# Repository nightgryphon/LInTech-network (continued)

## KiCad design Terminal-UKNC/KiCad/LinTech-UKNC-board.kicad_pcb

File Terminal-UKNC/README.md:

# LInTech - плата Терминальной Машины (ТМ) - клиента УКНЦ (Электроника МС 0511)

Плата воссоздана [Night Gryphon](https://github.com/nightgryphon) по имеющемуся у него в наличии оригиналу платы.

Прошивка платы маркирована "КЛС-ТМ-BD1 П1 В1 Т03"

Содержание:
- KiCad - исходный проект реконструкции платы в формате KiCad
- Gerbers - GERBER файлы для изготовления реплики
- LinTech-UKNC-board-BOM.html - BOM, список компонентов
- LinTech-UKNC-board.pdf - реконструированая схема платы
- Firmware - микропрограмма контроллера Intel 8031
- Reference_Photo - фото платы

На данный момент реальные платы по данной реконструкции не изготавливались / не тестировались, в проекте возможны неточности.

## Техническое описание
**[WIP]**

Плата устанавливается в боковой разъем СА вместо штатной сетевой карты УКНЦ и подключается к сети обычным (существующим) кабелем через стандартную коммутационную коробку учебной сети УКНЦ.

Плата построена на базе микроконтроллера Intel 8031 (ДД1).
 
Программа контроллера размещена во внешнем ПЗУ (ДД6). ОЗУ контроллера расширено 573РУ10 (ДД5). 

Адресное пространство памяти данных контроллера разделено на 2 части:
- В младшей части расположено дополнительное ОЗУ
- В старшей - порты контроллера 580ВВ55А (ДД13)

Обмен с линией осуществляется по последовательному порту (RXD/TXD)

На порт Р1 выведены сигналы шины периферийного процессора УКНЦ:
0. SYNC
1. DIN 
2. DOUT
3. WTBT
4. RPLY
5. DMGO
6. DMR 
7. SACK

**[ToDo]**
Описание работы с МПИ/QBUS и прерываний

MCU Р3.5 - разрешение векторных прерываний
ДД12 - адрес векторного прерывания ( 0b 1110 0x00 ; x = ~ ВВ55-PC.7)

### Интерфейс УКНЦ
[ToDo]

## Описание микропрограммы
[Требуется помощь]

## Сетевой протокол
[Требуется помощь]

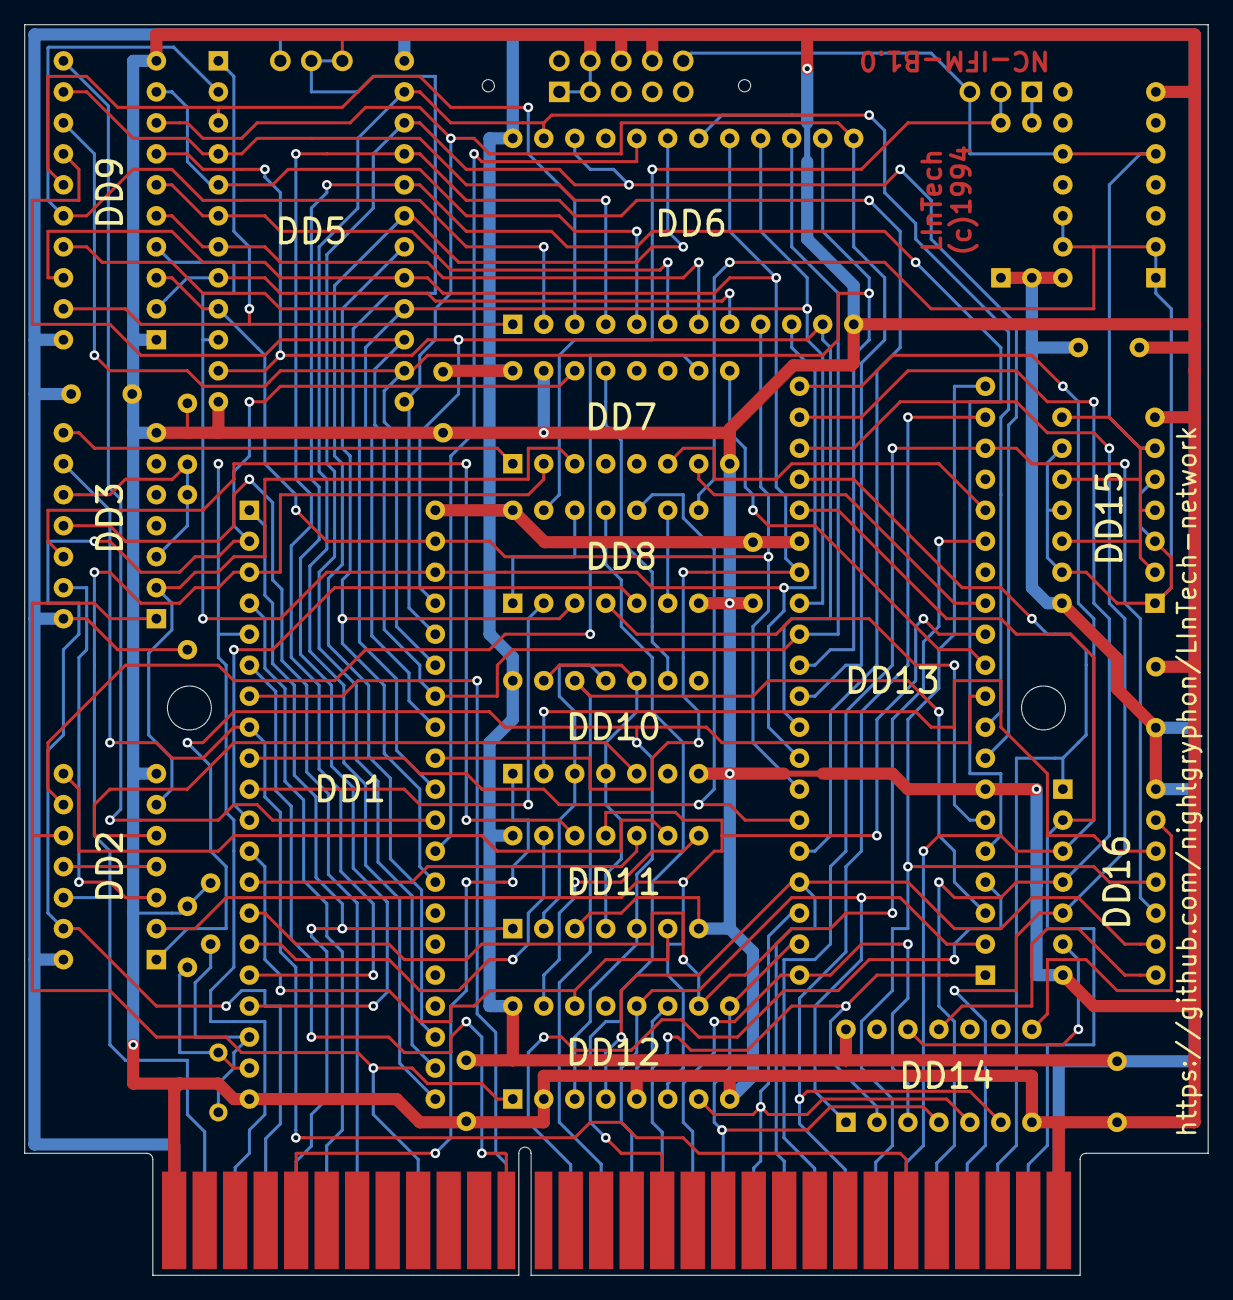
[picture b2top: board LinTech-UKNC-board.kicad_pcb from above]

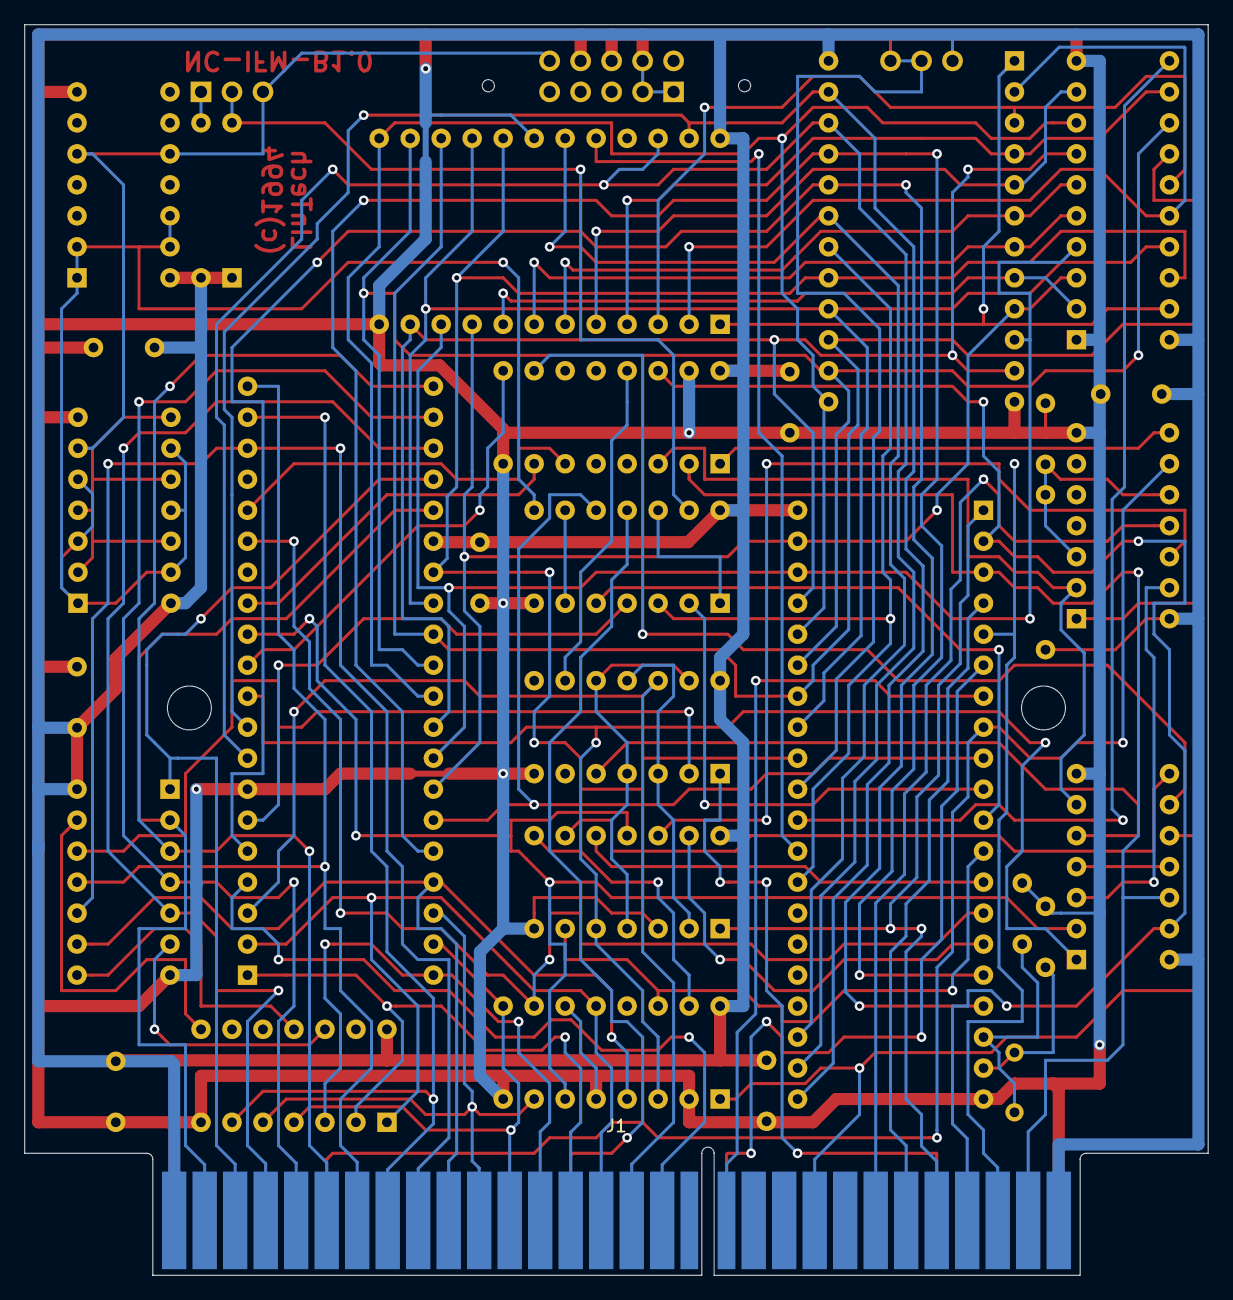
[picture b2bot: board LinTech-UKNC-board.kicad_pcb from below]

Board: 2 copper layers, 97.0 x 102.5 mm, 34 parts (2 on the bottom side), 93 nets.

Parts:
C1, C2: 18pf; C_Disc_D5.0mm_W2.5mm_P5.00mm
C3: 160pf; C_Disc_D5.0mm_W2.5mm_P5.00mm
C4, C5, C6, C7, C8, C9, C10: 150nf; C_Disc_D5.0mm_W2.5mm_P5.00mm
D1: КД522Б; D_A-405_P12.70mm_Horizontal
DD1: i8031; DIP-40_W15.24mm
DD2: 1533LA3; DIP-14_W7.62mm
DD3: 1533LA9; DIP-14_W7.62mm
DD5: 537RU10; DIP-24_W15.24mm
DD6: 573RF5; DIP-24_W15.24mm
DD7: 555ID4; DIP-16_W7.62mm
DD8: 1533LN1; DIP-14_W7.62mm
DD9: 1533IR22; DIP-20_W7.62mm
DD10: 555TM2; DIP-14_W7.62mm
DD11: 555LN1; DIP-14_W7.62mm
DD12: 1533KP11; DIP-16_W7.62mm
DD13: 580VV55A; DIP-40_W15.24mm
DD14: 1533LA2; DIP-14_W7.62mm
DD15: 155LP9; DIP-14_W7.62mm
DD16: 1533LE4; DIP-14_W7.62mm
J1: UKNC-CA
JP1: Jumper_3_Bridged12
LAN1: ОНП-КГ-56-10/33х7,4-В53; PinHeader_2x05_P2.54mm_Horizontal
Q1: КТ315Г; PinHeader_1x03_P2.54mm_Vertical
R1: 15K; R_Axial_DIN0309_L9.0mm_D3.2mm_P12.70mm_Horizontal
R2: 4K3; R_Axial_DIN0309_L9.0mm_D3.2mm_P12.70mm_Horizontal
WS1: DIP-14_W7.62mm
Y1: 12MHz; Crystal_HC18-U_Horizontal

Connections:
+5V: C4.2, C5.2, C6.2, C7.2, C8.1, C9.2, C10.2, D1.1, DD1.40, DD2.14, DD3.14, DD5.24, DD6.24, DD7.16, DD8.14, DD9.20, DD10.14, DD11.14, DD12.16, DD13.26, DD14.14, DD15.14, DD16.14, J1.1, J1.59, JP1.3, R1.1, R2.1, WS1.14
A16: DD10.1, J1.10
AD0: DD13.4, J1.27
AD1: DD10.12, DD13.3, J1.29
AD2: DD12.12, DD13.2, DD14.1, J1.31
AD3: DD13.1, DD14.2, J1.33
AD4: DD13.40, DD14.3, J1.35
AD5: DD12.9, DD13.39, DD14.4, J1.37
AD6: DD12.7, DD13.38, DD14.5, J1.39
AD7: DD12.4, DD13.37, DD16.9, J1.41
AD8: DD13.18, DD16.10, J1.43
AD9: DD13.19, DD14.6, J1.45
AD10: DD13.20, DD16.11, J1.47
AD11: DD13.21, DD16.3, J1.49
AD12: DD13.22, DD16.4, J1.51
AD13: DD13.23, DD16.5, J1.53
AD14: DD13.24, DD16.1, J1.55
AD15: DD13.25, DD16.2, J1.57
ALCO: DD8.11, J1.34
DIN: DD1.2, DD2.13, DD7.14, J1.7
DMGO: DD1.7, J1.23
DMR: DD1.6, J1.24
DOUT: DD1.3, DD2.12, DD7.2, J1.3
GND: C1.2, C2.2, C3.1, C4.1, C5.1, C6.1, C7.1, C8.2, C9.1, C10.1, DD1.20, DD2.7, DD3.7, DD5.12, DD6.12, DD6.18, DD7.8, DD7.15, DD8.7, DD9.1, DD9.10, DD10.7, DD11.3, DD11.7, DD12.2, DD12.5, DD12.8, DD12.11, DD13.7, DD14.7, DD15.7, DD16.7, J1.2, J1.60, JP1.1, LAN1.1, LAN1.3, LAN1.4, LAN1.6, LAN1.8, WS1.7
IAKO: DD2.10, DD3.1, DD12.1, J1.17
MCU_A8: DD1.21, DD5.23, DD6.23, DD13.9
MCU_A9: DD1.22, DD5.22, DD6.22, DD13.8
MCU_A10: DD1.23, DD5.19, DD6.19
MCU_A15: DD1.28, DD5.18, DD8.3
MCU_AD0: DD1.39, DD5.9, DD6.9, DD9.3, DD13.34
MCU_AD1: DD1.38, DD5.10, DD6.10, DD9.4, DD13.33
MCU_AD2: DD1.37, DD5.11, DD6.11, DD9.7, DD13.32
MCU_AD3: DD1.36, DD5.13, DD6.13, DD9.8, DD13.31
MCU_AD4: DD1.35, DD5.14, DD6.14, DD9.13, DD13.30
MCU_AD5: DD1.34, DD5.15, DD6.15, DD9.14, DD13.29
MCU_AD6: DD1.33, DD5.16, DD6.16, DD9.17, DD13.28
MCU_AD7: DD1.32, DD5.17, DD6.17, DD9.18, DD13.27
MCU_ALE: DD1.30, DD9.11
MCU_EA: DD1.31, JP1.2
MCU_INT0: DD1.12, DD11.6, DD12.14
MCU_INT1: DD1.13, DD11.10
MCU_P3-4: DD1.14, DD12.10, DD13.15
MCU_P3-5: DD1.15, DD11.13
MCU_PSEN: DD1.29, DD6.20
MCU_RD: DD1.17, DD5.20, DD13.5
MCU_RESET: DD1.9, DD8.10, DD13.35
MCU_RXD: DD1.10, DD8.2
MCU_TXD: DD1.11, DD8.5
MCU_WR: DD1.16, DD5.21, DD13.36
M_A0: DD5.8, DD6.8, DD9.2
M_A1: DD5.7, DD6.7, DD9.5
M_A2: DD5.6, DD6.6, DD9.6
M_A3: DD5.5, DD6.5, DD9.9
M_A4: DD5.4, DD6.4, DD9.12
M_A5: DD5.3, DD6.3, DD9.15
M_A6: DD5.2, DD6.2, DD9.16
M_A7: DD5.1, DD6.1, DD9.19
unnamed: C1.1, DD1.19, Y1.1
unnamed: C2.1, DD1.18, Y1.2
unnamed: C3.2, DD3.3, DD3.10, R1.2
unnamed: D1.2, DD8.13, Q1.2
unnamed: DD2.3, DD3.13
unnamed: DD2.6, DD3.2, DD7.3
unnamed: DD2.9, DD7.10
unnamed: DD2.4, DD2.11
unnamed: DD3.8, DD7.1
unnamed: DD8.1, DD8.12
unnamed: DD8.6, DD8.9
unnamed: DD10.2, DD16.12
unnamed: DD2.5, DD10.5
unnamed: DD7.13, DD10.9
unnamed: DD10.4, DD10.10, DD10.13, DD11.4
unnamed: DD10.3, DD10.11, DD11.2
unnamed: DD2.1, DD11.5, DD12.3, DD13.10
unnamed: DD11.8, DD12.15
unnamed: DD2.8, DD11.9
unnamed: DD2.2, DD11.11, DD12.6, DD13.12
unnamed: DD3.12, DD11.12
unnamed: DD8.4, DD13.6
unnamed: DD7.9, DD13.11
unnamed: DD7.7, DD13.13
unnamed: DD7.6, DD13.16
unnamed: DD14.8, DD16.13
unnamed: DD14.11, DD16.8
unnamed: DD14.12, DD16.6
unnamed: DD8.8, DD15.1, DD15.3, DD15.5, DD15.9, DD15.11, DD15.13, WS1.1, WS1.2, WS1.12, WS1.13
unnamed: DD15.2, DD15.4, DD15.6, DD15.8, DD15.10, DD15.12, LAN1.10, Q1.3, WS1.5, WS1.10
unnamed: Q1.1, R2.2
RPLY: DD1.5, J1.5
SACK: DD1.8, DD3.9, J1.50
SYNC: DD1.1, DD11.1, J1.9
VIRQ: DD3.11, J1.13
WTBT: DD1.4, J1.11

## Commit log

2023-10-15 README Draft 1
2023-10-16 Initial
2023-10-17 Initial 2
2023-10-18 README edit
2023-10-19 Update GM schematic, README, split LInTech software archive
2023-10-19 Update GM board silkscreen and 3D render
2023-10-19 FIX charset
2023-10-19 README Links
2023-10-19 Add img to front page
2023-10-20 Update README.md
    fix img
2023-10-20 Fix typos
2023-10-20 Update README.md add images
2023-10-20 Update README.md fix links
2023-10-21 Fix footprint drill diameters
2023-10-21 Fix URLs
2023-10-21 Adjust test pads, track width, DB9
2023-10-21 Rename root folders
2023-10-21 Corvette stub
2023-10-22 Remove outdated NC-ACM-2.3E-1996 reference photos
2023-10-22 Add new reference photos
2023-10-22 Rename NC-ACM-2.2-1994 references
2023-10-22 Terminal-BK0010 References Update
2023-10-22 Terminal-UKNC References Update
2023-10-25 FIX DD9 pin 13 wire, add R15 placeholder
2023-10-25 README fix
2023-10-28 Server-IBM-PC add some new photo references
2023-10-28 Add Korvet Firmware
2023-10-28 Add Terminal-Corvette References
2023-10-28 Update README.md
    Small img fix
2023-10-28 Server board NC-ACM-2.3E
2023-10-30 Anton Mironov re-readed Corvette-T08 firmware right
2023-10-30 Update Corvette README
2023-10-30 Revert "Update Corvette README"
    This reverts commit bf77767a2e7c51ede5fa806b1ac09b1c9ae51b82.
2023-10-30 Revert "Anton Mironov re-readed Corvette-T08 firmware right"
    This reverts commit cc20e0ffb68a49a786e7fd9d18c8fe8b8090eb0b.
2024-10-04 Add UKNC TM firmware by @Yrust
